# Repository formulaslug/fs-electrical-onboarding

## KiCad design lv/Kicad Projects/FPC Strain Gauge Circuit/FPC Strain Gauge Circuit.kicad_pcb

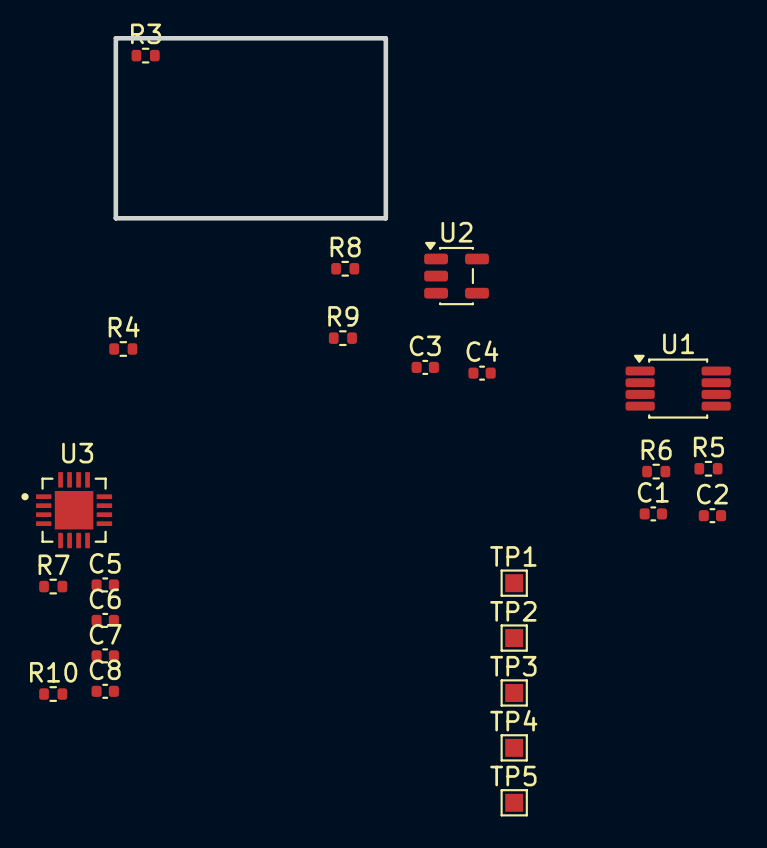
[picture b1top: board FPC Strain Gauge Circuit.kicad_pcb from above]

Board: 4 copper layers, 15.0 x 10.0 mm, 24 parts (0 on the bottom side), 15 nets, no tracks yet.

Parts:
C1, C6: 10nF; C_0402_1005Metric
C2, C5, C7, C8: 100nF; C_0402_1005Metric
C3, C4: 1uF; C_0402_1005Metric
R3, R4: 350; R_0402_1005Metric
R5, R6: 100; R_0402_1005Metric
R7, R10: 1k; R_0402_1005Metric
R8, R9: 10k; R_0402_1005Metric
TP1, TP2, TP3, TP4, TP5: TestPoint; TestPoint_Pad_1.0x1.0mm
U1: INA333xxDGK; VSSOP-8_3x3mm_P0.65mm
U2: OPA333xxDBV; SOT-23-5
U3: ADS1220IRVAR; QFN50P350X350X100-17N

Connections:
+3V3_A: C2.1, C3.1, C5.1, C7.1, C8.1, R8.1, TP1.1 (1_1), U1.7 (V+), U2.5 (V+), U3.10 (AVDD), U3.11 (DVDD)
/ADC_MISO: TP5.1 (1_1), U3.13 (DOUT/DRDY)
/ADC_MOSI: TP4.1 (1_1), U3.14 (DIN)
/ADC_SCLK: TP3.1 (1_1), U3.15 (SCLK)
/BRIDGE_N: R3.1, R6.1
/BRIDGE_P: R4.1, R5.1
/LOAD_SIGNAL: C6.1, R10.2, U3.9 (ALNO/REFP1)
/VREF_1V65: U1.5 (Ref), U2.1, U2.4 (-), U3.8 (AIN1)
/VREF_RAW: C4.1, R8.2, R9.1, U2.3 (+)
AGND: C2.2, C3.2, C4.2, C5.2, C6.2, C7.2, C8.2, R3.2, R4.2, R9.2, TP2.1 (1_1), U1.4 (V-), U2.2 (V-), U3.1 (CLK), U3.2 (DGND), U3.3 (AVSS), U3.16 (CS)
unnamed: R7.1, U1.8 (Rg)
unnamed: R7.2, U1.1 (Rg)
unnamed: R10.1, U1.6
unnamed: C1.2, R5.2, U1.3 (+)
unnamed: C1.1, R6.2, U1.2 (-)

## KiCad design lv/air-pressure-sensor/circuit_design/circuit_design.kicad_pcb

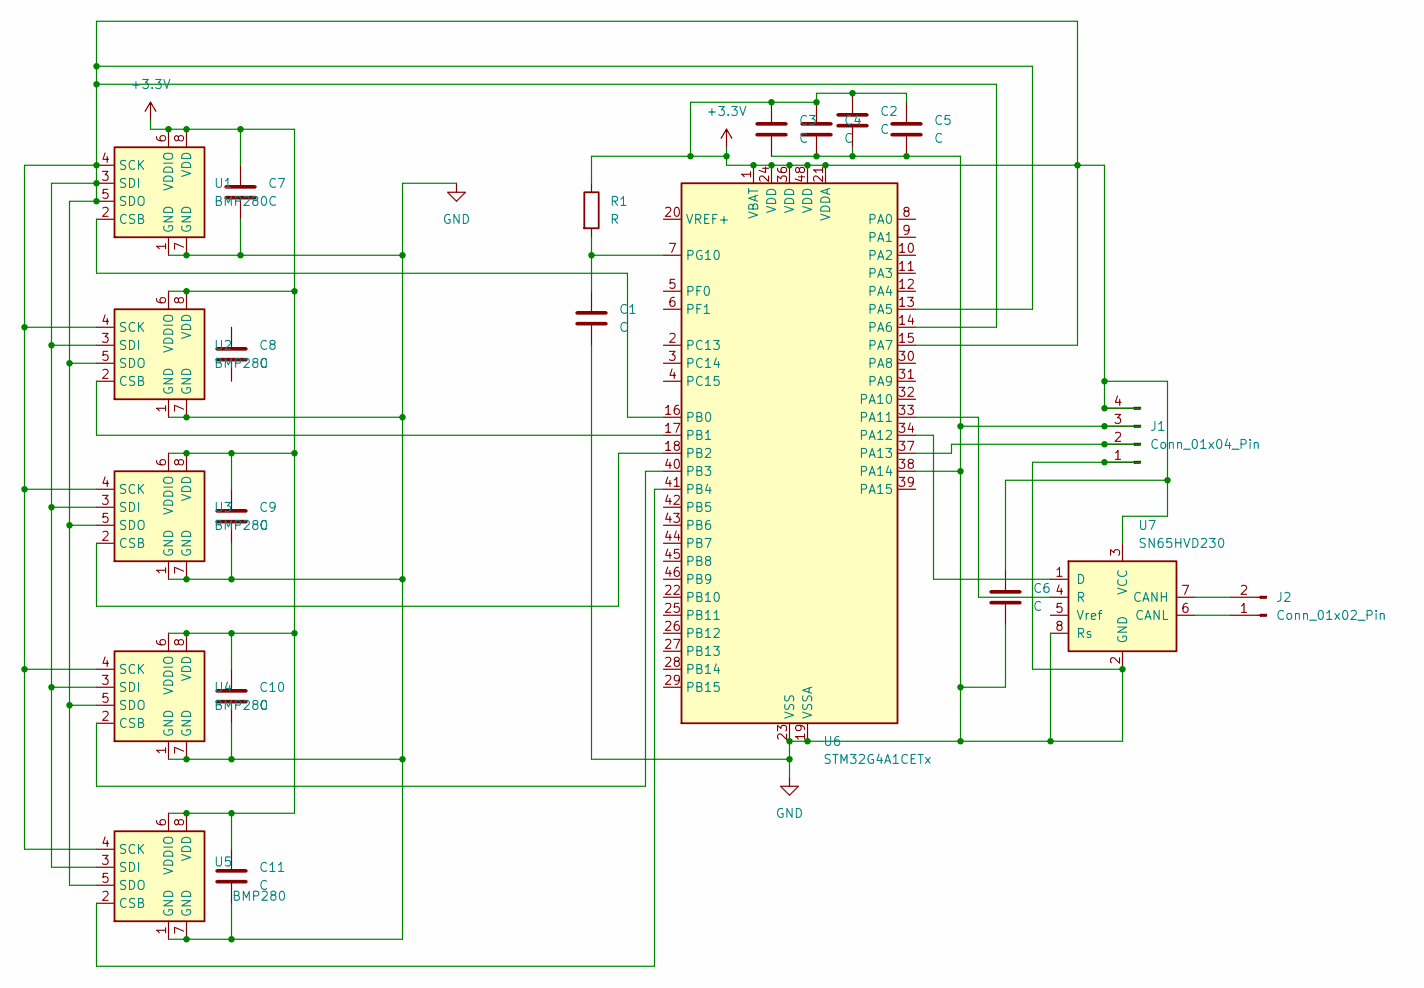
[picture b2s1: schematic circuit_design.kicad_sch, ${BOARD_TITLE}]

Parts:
C1, C2, C3, C4, C5, C6, C7, C8, C9, C10, C11: C; C_0805_2012Metric
J1: Conn_01x04_Pin; PinHeader_1x04_P2.54mm_Vertical
J2: Conn_01x02_Pin; PinHeader_1x02_P2.54mm_Vertical
R1: R; R_0805_2012Metric
U1, U2, U3, U4, U5: BMP280; Bosch_LGA-8_2x2.5mm_P0.65mm_ClockwisePinNumbering
U6: STM32G4A1CETx; LQFP-48_7x7mm_P0.5mm
U7: SN65HVD230; SOIC-8_3.9x4.9mm_P1.27mm

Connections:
+3.3V: C2.1, C3.1, C4.1, C5.1, C6.1, C7.1, C9.1, C10.1, C11.1, J1.4, R1.1, U1.3 (SDI), U1.4 (SCK), U1.5 (SDO), U1.6 (VDDIO), U1.8 (VDD), U2.3 (SDI), U2.4 (SCK), U2.5 (SDO), U2.6 (VDDIO), U2.8 (VDD), U3.3 (SDI), U3.4 (SCK), U3.5 (SDO), U3.6 (VDDIO), U3.8 (VDD), U4.3 (SDI), U4.4 (SCK), U4.5 (SDO), U4.6 (VDDIO), U4.8 (VDD), U5.3 (SDI), U5.4 (SCK), U5.5 (SDO), U5.6 (VDDIO), U5.8 (VDD), U6.1 (VBAT), U6.13 (PA5), U6.14 (PA6), U6.15 (PA7), U6.21 (VDDA), U6.24 (VDD), U6.36 (VDD), U6.48 (VDD), U7.3 (VCC)
GND: C1.2, C2.2, C3.2, C4.2, C5.2, C6.2, C7.2, C9.2, C10.2, C11.2, J1.1, J1.3, U1.1 (GND), U1.7 (GND), U2.1 (GND), U2.7 (GND), U3.1 (GND), U3.7 (GND), U4.1 (GND), U4.7 (GND), U5.1 (GND), U5.7 (GND), U6.19 (VSSA), U6.23 (VSS), U6.35 (VSS), U6.38 (PA14), U6.47 (VSS), U7.2 (GND), U7.8 (Rs)
unnamed: J1.2, U6.37 (PA13)
unnamed: J2.1, U7.6 (CANL)
unnamed: J2.2, U7.7 (CANH)
unnamed: U1.2 (CSB), U6.16 (PB0)
unnamed: U2.2 (CSB), U6.17 (PB1)
unnamed: U3.2 (CSB), U6.18 (PB2)
unnamed: U4.2 (CSB), U6.40 (PB3)
unnamed: U5.2 (CSB), U6.41 (PB4)
unnamed: U6.33 (PA11), U7.4 (R)
unnamed: U6.34 (PA12), U7.1 (D)
unnamed: C1.1, R1.2, U6.7 (PG10)

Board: 2 copper layers, 21 parts (0 on the bottom side), 13 nets, no tracks yet.

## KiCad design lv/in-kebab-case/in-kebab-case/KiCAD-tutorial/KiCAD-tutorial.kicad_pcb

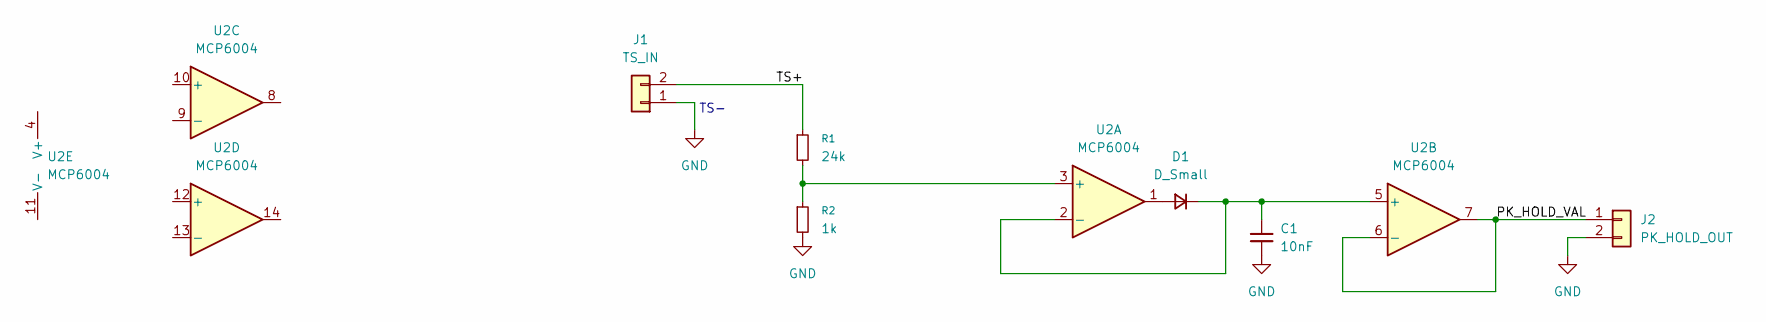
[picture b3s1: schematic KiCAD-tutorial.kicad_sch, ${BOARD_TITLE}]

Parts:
C1: 10nF; C_0603_1608Metric
D1: D_Small; D_0603_1608Metric
J1: TS_IN; PinHeader_1x02_P1.00mm_Horizontal
J2: PK_HOLD_OUT; PinHeader_1x02_P1.00mm_Horizontal
R1: 24k; R_0603_1608Metric
R2: 1k; R_0603_1608Metric
U2: MCP6004; SOIC-14_3.9x8.7mm_P1.27mm

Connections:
/PK_HOLD_VAL: J2.1, U2.6 (-), U2.7
/TS+: J1.2, R1.1
GND: C1.2, J1.1, J2.2, R2.2
unnamed: D1.2 (A), U2.1
unnamed: C1.1, D1.1 (K), U2.2 (-), U2.5 (+)
unnamed: R1.2, R2.1, U2.3 (+)

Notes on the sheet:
TS-

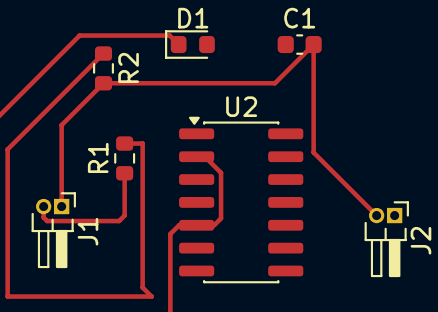
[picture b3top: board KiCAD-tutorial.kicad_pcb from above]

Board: 2 copper layers, 7 parts (0 on the bottom side), 6 nets.

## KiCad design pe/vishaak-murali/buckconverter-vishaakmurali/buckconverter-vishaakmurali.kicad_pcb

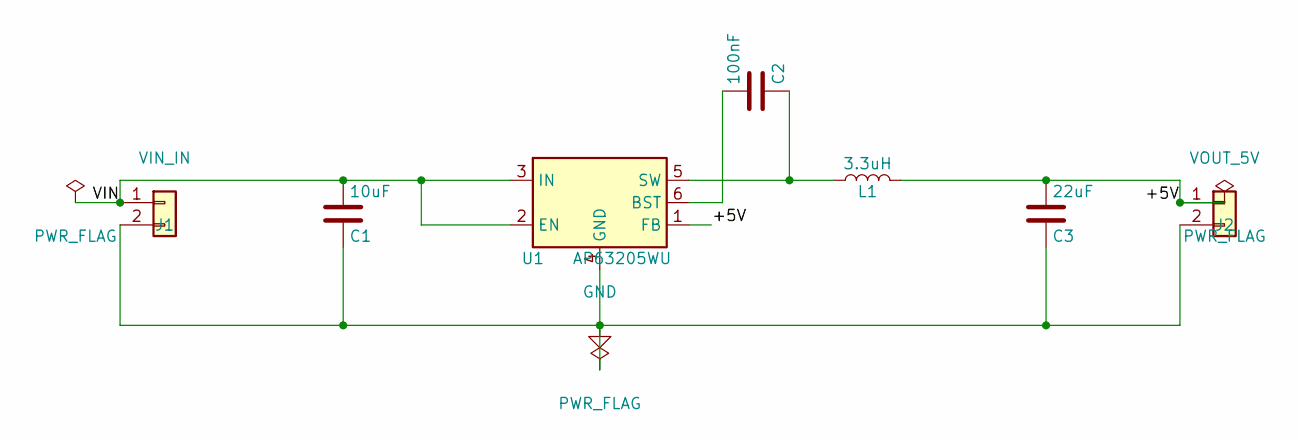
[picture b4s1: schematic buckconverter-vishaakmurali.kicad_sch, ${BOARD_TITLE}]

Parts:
C1: 10uF; C_0805_2012Metric
C2: 100nF; C_0603_1608Metric
C3: 22uF; C_0805_2012Metric
J1: VIN_IN; PinHeader_1x02_P2.54mm_Vertical
J2: VOUT_5V; PinHeader_1x02_P2.54mm_Vertical
L1: 3.3uH; L_Bourns_SRR1260
U1: AP63205WU; TSOT-23-6

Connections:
+5V: C3.1, J2.1, L1.2, U1.1 (FB)
GND: C1.2, C3.2, J1.2, J2.2, U1.4 (GND)
unnamed: C2.1, U1.6 (BST)
unnamed: C2.2, L1.1, U1.5 (SW)
VIN: C1.1, J1.1, U1.2 (EN), U1.3 (IN)

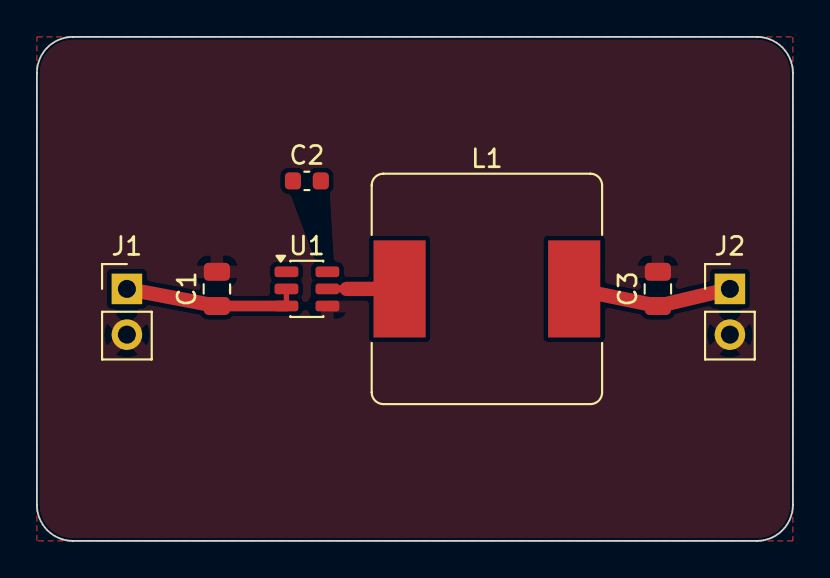
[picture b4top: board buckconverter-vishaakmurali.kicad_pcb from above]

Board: 2 copper layers, 42.0 x 28.0 mm, 7 parts (0 on the bottom side), 5 nets.
